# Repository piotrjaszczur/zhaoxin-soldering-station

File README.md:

# zhaoxin-soldering-station
Project for microcontrollers course at AGH. Soldering station control unit for the Zhaoxin 936 soldering iron

The schematic and the board created for the project for the microcontrollers course at AGH. 
It was based around the "Blue Pill" STM32 Development Board with STM32f103c8t6 MCU. It provided the temperature reading based on the ADC measuring of the voltage on the soldering iron termistor. IRF4905 PMOS transistor was driven by the PWM signal with the duty cycle depending on the current temperature reading. The rotary encoder allowed to change the desired temperature and the 4 microswitches allowed to choose one of the preset 4 different temperatures.

It is planned to be used with a 24V switching power supply.

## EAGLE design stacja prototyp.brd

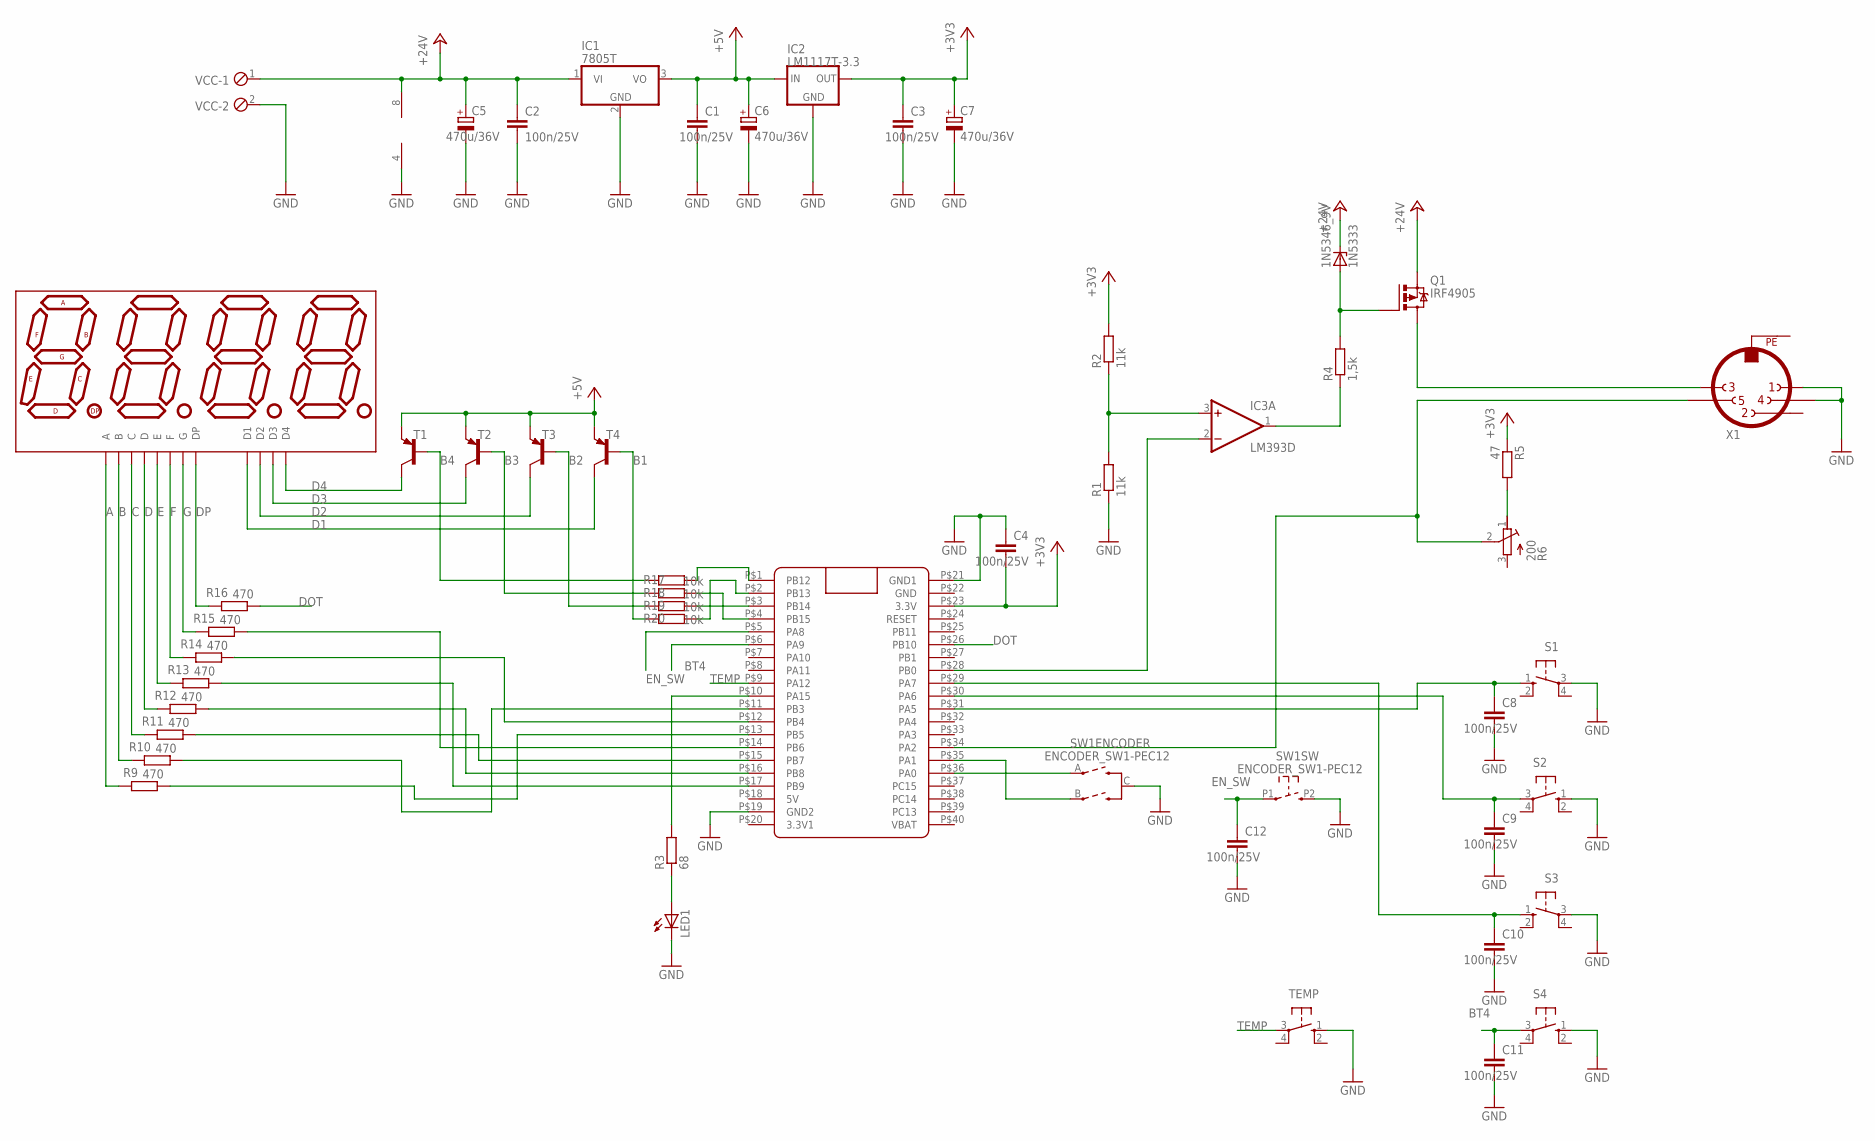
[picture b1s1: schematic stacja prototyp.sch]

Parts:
1N5346_9V: 1N5333; C1702-15
C1, C2, C3, C4, C8, C9, C10, C11, C12: 100n/25V; C1206
C5, C6, C7: 470u/36V; E2,5-5
DISP1: ATA8041ARBJ; 7-SEGMENT-4DIGIT-20MM
IC1: 7805T; TO220H
IC2: LM1117T-3.3; TO220
IC3: LM393D; SO08
LED1: LED5MM
Q1: IRF4905; TO220BH
R1, R2: 11k; R0805
R3: 68; R0805
R4: 1,5k; 0207/15
R5: 47; 0207/15
R6: 200; RTRIM43P
R9, R10, R11, R12, R13, R14, R15, R16: 470; M0805
R17, R18, R19, R20: 10k; M0805
S1, S2, S3, S4: 10-XX; B3F-10XX
SW1: ENCODER_SW1-PEC12; PEC12_INCREMENTAL_ENCODER
T1, T2, T3, T4: BC857B-PNP-SOT23-BEC; SOT23-BEC
TEMP: 10-XX; B3F-10XX
U$1: BLUE_PILL
VCC: MPT2; 2POL254
X1: MAB5SV

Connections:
+3V3: C3.1, C4.2, C7.+, IC2.2 (OUT), R2.2, R5.1, U$1.P$23 (3.3V)
+5V: C1.1, C6.+, IC1.3 (VO), IC2.3 (IN), T1.E, T2.E, T3.E, T4.E
+24V: 1N5346_9V.C, C2.1, C5.+, IC1.1 (VI), IC3.8 (V+), Q1.S, VCC.1
A: DISP1.11 (A), R9.2
B: DISP1.7 (B), R10.2
B1: R20.2, T4.B
B2: R19.2, T3.B
B3: R18.2, T2.B
B4: R17.2, T1.B
BT4: C11.1, S4.3, U$1.P$6 (PA9)
C: DISP1.4 (C), R11.2
D: DISP1.2 (D), R12.2
D1: DISP1.12 (D1), T4.C
D2: DISP1.9 (D2), T3.C
D3: DISP1.8 (D3), T2.C
D4: DISP1.6 (D4), T1.C
DOT: R16.1, U$1.P$26 (PB10)
DP: DISP1.3 (DP), R16.2
E: DISP1.1 (E), R13.2
EN_SW: C12.1, SW1.P1 (1), U$1.P$5 (PA8)
F: DISP1.10 (F), R14.2
G: DISP1.5 (G), R15.2
GND: C1.2, C2.2, C3.2, C4.1, C5.-, C6.-, C7.-, C8.2, C9.2, C10.2, C11.2, C12.2, IC1.2 (GND), IC2.1 (GND), IC3.4 (V-), LED1.K (C), R1.1, S1.3, S2.1 (S), S3.3, S4.1 (S), SW1.C, SW1.P2 (2), TEMP.1 (S), U$1.P$19 (GND2), U$1.P$21 (GND1), VCC.2, X1.1, X1.4
unnamed: IC3.2 (-IN), U$1.P$28 (PB0)
unnamed: C8.1, S1.1 (S), U$1.P$31 (PA5)
unnamed: C9.1, S2.3, U$1.P$30 (PA6)
unnamed: IC3.3 (+IN), R1.2, R2.1
unnamed: R6.2 (S), U$1.P$34 (PA2), X1.5
unnamed: IC3.1 (OUT), R4.1
unnamed: 1N5346_9V.A, Q1.G, R4.2
unnamed: Q1.D, X1.3
unnamed: SW1.A, U$1.P$36 (PA0)
unnamed: SW1.B, U$1.P$35 (PA1)
unnamed: LED1.A, R3.1
unnamed: R3.2, U$1.P$10 (PA15)
unnamed: R5.2, R6.1 (E)
unnamed: C10.1, S3.1 (S), U$1.P$29 (PA7)
unnamed: R18.1, U$1.P$4 (PB15)
unnamed: R19.1, U$1.P$3 (PB14)
unnamed: R17.1, U$1.P$1 (PB12)
unnamed: R20.1, U$1.P$2 (PB13)
unnamed: R13.1, U$1.P$17 (PB9)
unnamed: R12.1, U$1.P$16 (PB8)
unnamed: R11.1, U$1.P$15 (PB7)
unnamed: R15.1, U$1.P$14 (PB6)
unnamed: R9.1, U$1.P$13 (PB5)
unnamed: R14.1, U$1.P$12 (PB4)
unnamed: R10.1, U$1.P$11 (PB3)
PE: X1.PE
TEMP: TEMP.3, U$1.P$9 (PA12)

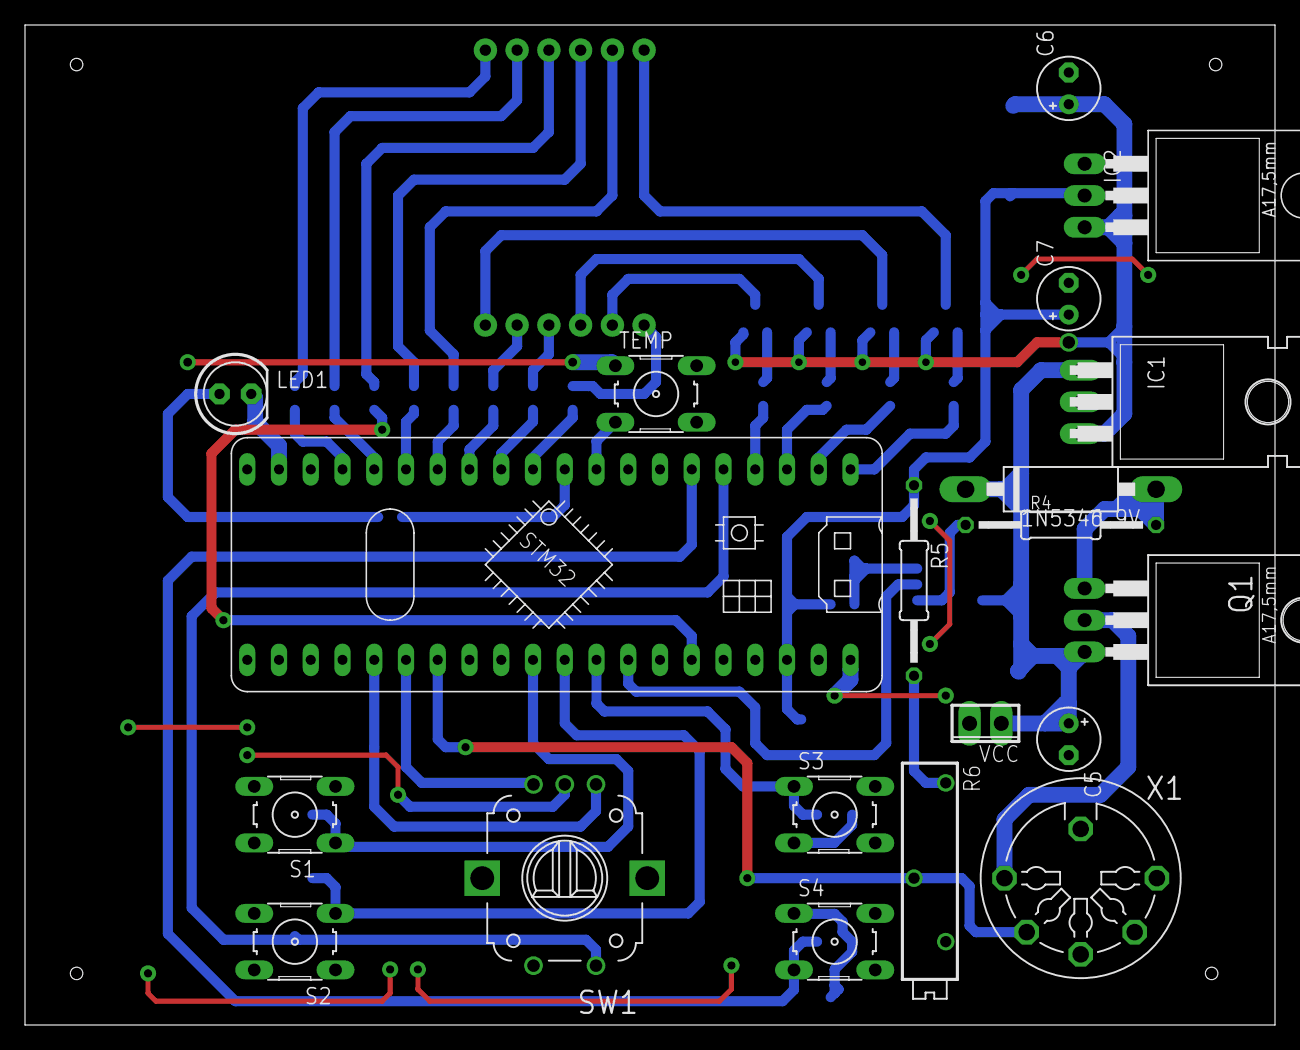
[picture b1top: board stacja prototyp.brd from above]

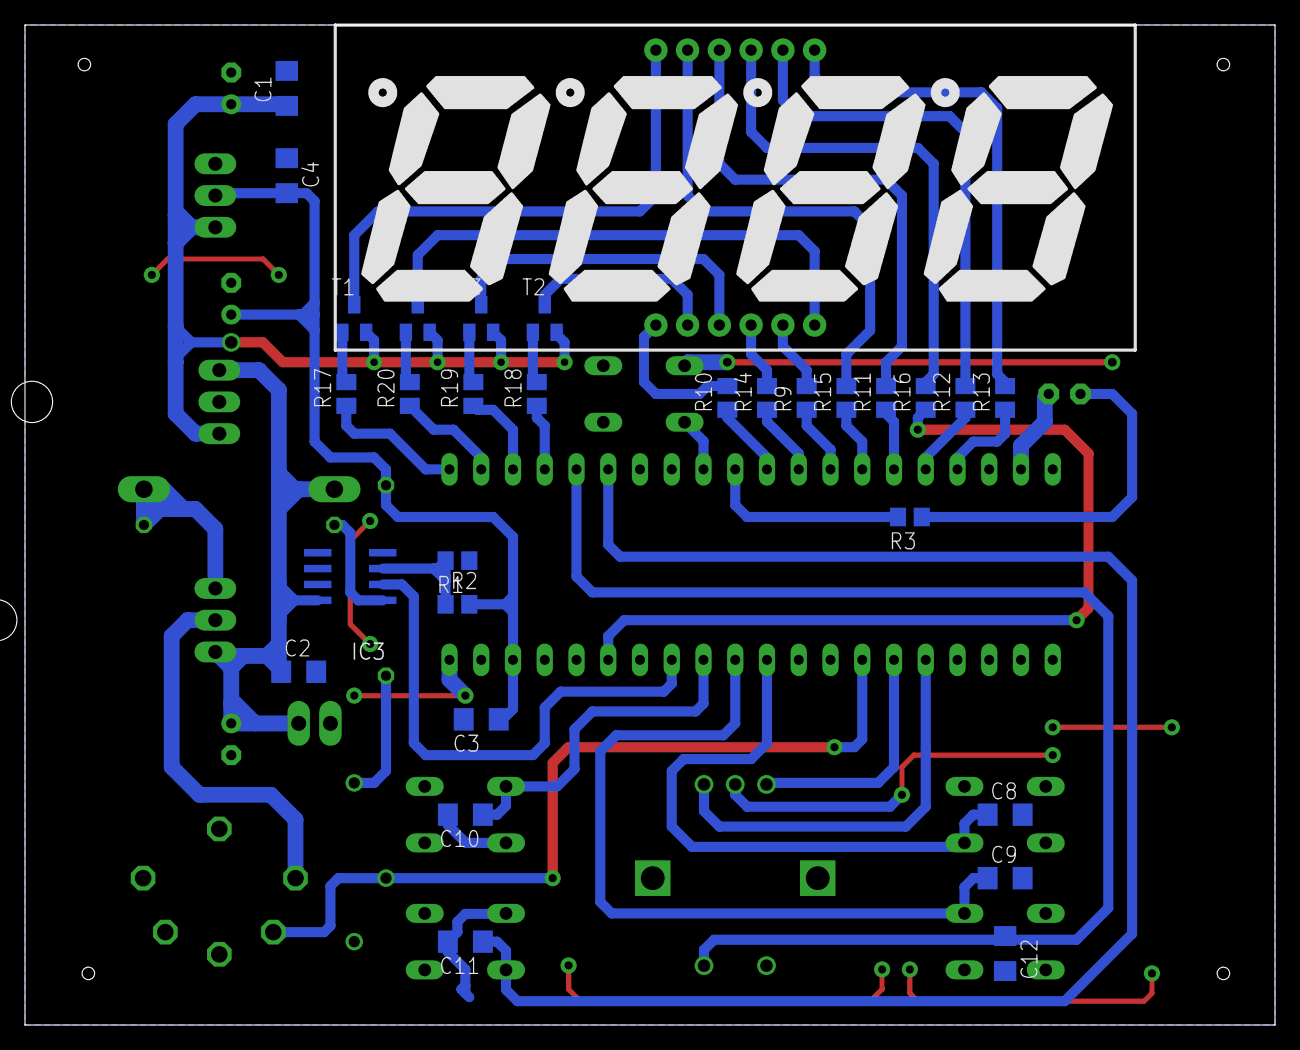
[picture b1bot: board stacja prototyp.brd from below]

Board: 2 copper layers, 100.0 x 80.0 mm, 50 parts (30 on the bottom side), 49 nets.

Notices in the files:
parts and their libraries:
SparkFun-LED: Licensing: Creative Commons ShareAlike 4.0 International - https://creativecommons.org/licenses/by-sa/4.0
